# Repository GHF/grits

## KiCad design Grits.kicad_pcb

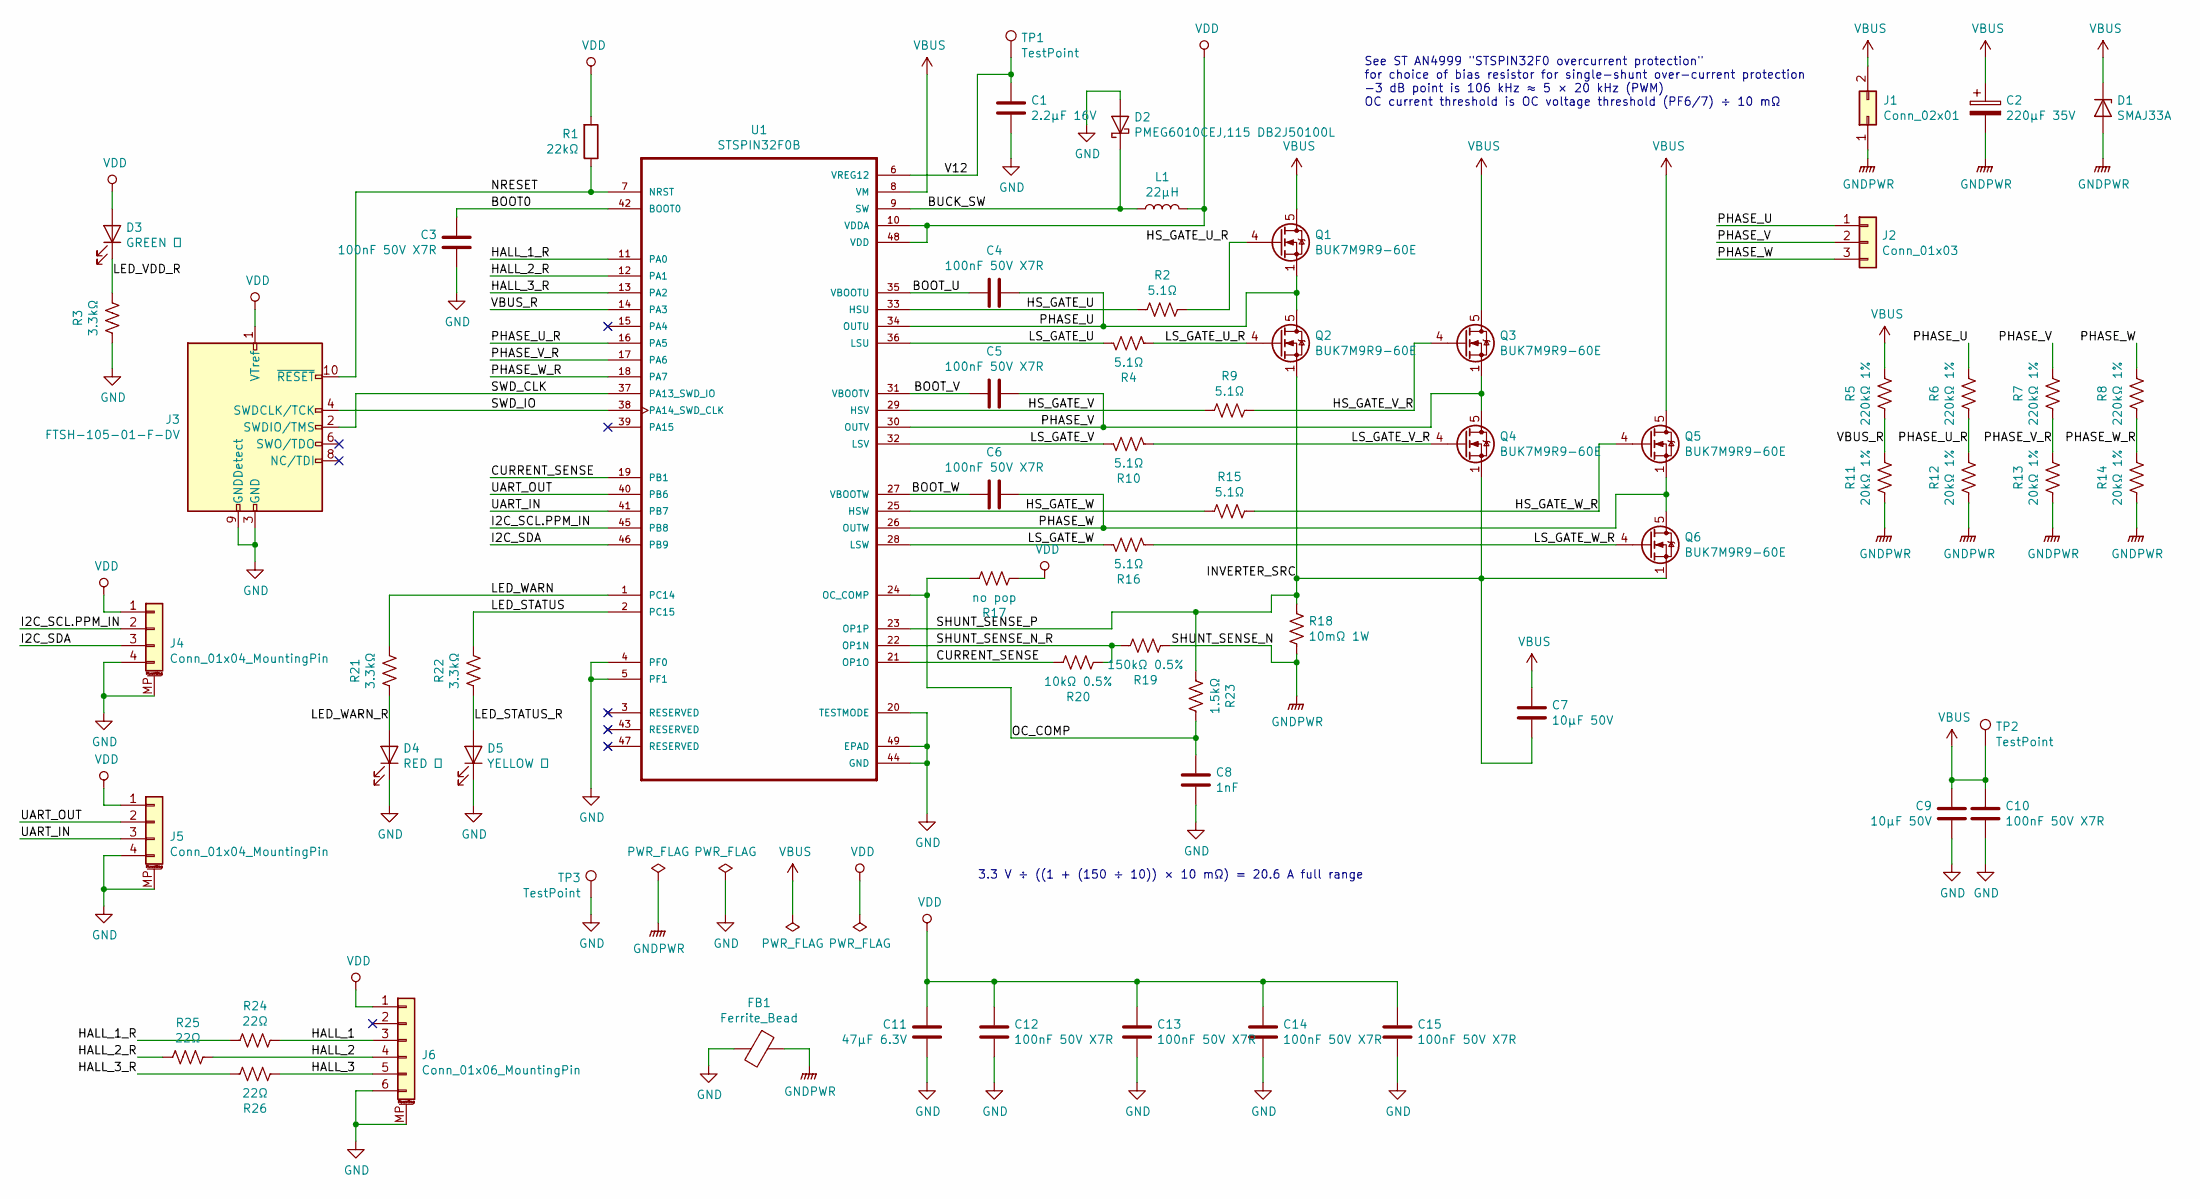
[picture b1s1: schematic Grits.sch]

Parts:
C1: 2.2µF 16V; C_0603_1608Metric
C2: 220µF 35V; CP_Elec_8x10.5
C3, C4, C5, C6, C10, C12, C13, C14, C15: 100nF 50V X7R; C_0603_1608Metric
C7, C9: 10µF 50V; C_1206_3216Metric
C8: 1nF; C_0603_1608Metric
C11: 47µF 6.3V; C_0805_2012Metric
D1: SMAJ33A; D_SMA
D2: PMEG6010CEJ,115 DB2J50100L; D_SOD-323F
D3: GREEN 绿; LED_0805_2012Metric
D4: RED 红; LED_0805_2012Metric
D5: YELLOW 黄; LED_0805_2012Metric
FB1: Ferrite_Bead; L_0603_1608Metric
J1: Conn_02x01; Molex_Micro-Fit_3.0_43045-0200_2x01_P3.00mm_Horizontal
J2: Conn_01x03; Molex_Micro-Fit_3.0_43650-0300_1x03_P3.00mm_Horizontal
J3: FTSH-105-01-F-DV; PinHeader_2x05_P1.27mm_Vertical_SMD
J4, J5: Conn_01x04_MountingPin; JST_GH_SM04B-GHS-TB_1x04-1MP_P1.25mm_Horizontal
J6: Conn_01x06_MountingPin; JST_GH_BM06B-GHS-TBT_1x06-1MP_P1.25mm_Vertical
L1: 22µH; L_1008_2520Metric
Q1, Q2, Q3, Q4, Q5, Q6: BUK7M9R9-60E; LFPAK33
R1: 22kΩ; R_0603_1608Metric
R2, R4, R9, R10, R15, R16: 5.1Ω; R_0603_1608Metric
R3, R21, R22: 3.3kΩ; R_0603_1608Metric
R5, R6, R7, R8: 220kΩ 1%; R_0603_1608Metric
R11, R12, R13, R14: 20kΩ 1%; R_0603_1608Metric
R17: no pop; R_0603_1608Metric
R18: 10mΩ 1W; R_1206_3216Metric
R19: 150kΩ 0.5%; R_0603_1608Metric
R20: 10kΩ 0.5%; R_0603_1608Metric
R23: 1.5kΩ; R_0603_1608Metric
R24, R25, R26: 22Ω; R_0603_1608Metric
TP1, TP2, TP3: TestPoint; TestPoint_Pad_D1.0mm
U1: STSPIN32F0B; VQFN-48-1EP_7x7mm_P0.5mm_EP2.8x2.8mm

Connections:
/BOOT0: C3.2, U1.42 (BOOT0)
/BOOT_U: C4.2, U1.35 (VBOOTU)
/BOOT_V: C5.2, U1.31 (VBOOTV)
/BOOT_W: C6.2, U1.27 (VBOOTW)
/BUCK_SW: D2.1 (K), L1.1, U1.9 (SW)
/CURRENT_SENSE: R20.1, U1.19 (PB1), U1.21 (OP1O)
/HALL_1: J6.3, R24.1
/HALL_1_R: R24.2, U1.11 (PA0)
/HALL_2: J6.4, R25.1
/HALL_2_R: R25.2, U1.12 (PA1)
/HALL_3: J6.5, R26.2
/HALL_3_R: R26.1, U1.13 (PA2)
/HS_GATE_U: R2.2, U1.33 (HSU)
/HS_GATE_U_R: Q1.4 (G), R2.1
/HS_GATE_V: R9.2, U1.29 (HSV)
/HS_GATE_V_R: Q3.4 (G), R9.1
/HS_GATE_W: R15.2, U1.25 (HSW)
/HS_GATE_W_R: Q5.4 (G), R15.1
/I2C_SCL.PPM_IN: J4.2, U1.45 (PB8)
/I2C_SDA: J4.3, U1.46 (PB9)
/INVERTER_SRC: C7.2, Q2.1 (S), Q2.2 (S), Q2.3 (S), Q4.1 (S), Q4.2 (S), Q4.3 (S), Q6.1 (S), Q6.2 (S), Q6.3 (S), R18.1, R23.2, U1.23 (OP1P)
/LED_STATUS: R22.1, U1.2 (PC15)
/LED_STATUS_R: D5.2 (A), R22.2
/LED_VDD_R: D3.1 (K), R3.1
/LED_WARN: R21.1, U1.1 (PC14)
/LED_WARN_R: D4.2 (A), R21.2
/LS_GATE_U: R4.2, U1.36 (LSU)
/LS_GATE_U_R: Q2.4 (G), R4.1
/LS_GATE_V: R10.2, U1.32 (LSV)
/LS_GATE_V_R: Q4.4 (G), R10.1
/LS_GATE_W: R16.2, U1.28 (LSW)
/LS_GATE_W_R: Q6.4 (G), R16.1
/NRESET: J3.10 (~RESET~), R1.1, U1.7 (NRST)
/OC_COMP: C8.1, R17.1, R23.1, U1.24 (OC_COMP)
/PHASE_U: C4.1, J2.1, Q1.1 (S), Q1.2 (S), Q1.3 (S), Q2.5 (D), R6.1, U1.34 (OUTU)
/PHASE_U_R: R6.2, R12.1, U1.16 (PA5)
/PHASE_V: C5.1, J2.2, Q3.1 (S), Q3.2 (S), Q3.3 (S), Q4.5 (D), R7.1, U1.30 (OUTV)
/PHASE_V_R: R7.2, R13.1, U1.17 (PA6)
/PHASE_W: C6.1, J2.3, Q5.1 (S), Q5.2 (S), Q5.3 (S), Q6.5 (D), R8.1, U1.26 (OUTW)
/PHASE_W_R: R8.2, R14.1, U1.18 (PA7)
/SHUNT_SENSE_N_R: R19.1, R20.2, U1.22 (OP1N)
/SWD_CLK: J3.2 (SWDIO/TMS), U1.37 (PA13_SWD_IO)
/SWD_IO: J3.4 (SWDCLK/TCK), U1.38 (PA14_SWD_CLK)
/UART_IN: J5.3, U1.41 (PB7)
/UART_OUT: J5.2, U1.40 (PB6)
/V12: C1.1, TP1.1, U1.6 (VREG12)
/VBUS_R: R5.2, R11.1, U1.14 (PA3)
GND: C1.2, C3.1, C8.2, C9.2, C10.2, C11.2, C12.2, C13.2, C14.2, C15.2, D2.2 (A), D4.1 (K), D5.1 (K), FB1.2, J3.3 (GND), J3.5 (GND), J3.9 (GNDDetect), J4.4, J4.MP (MountPin), J5.4, J5.MP (MountPin), J6.6, J6.MP (MountPin), R3.2, TP3.1, U1.4 (PF0), U1.5 (PF1), U1.20 (TESTMODE), U1.44 (GND), U1.49 (EPAD)
GNDPWR: C2.2, D1.2 (A), FB1.1, J1.1, R11.2, R12.2, R13.2, R14.2, R18.2, R19.2
VBUS: C2.1, C7.1, C9.1, C10.1, D1.1 (K), J1.2, Q1.5 (D), Q3.5 (D), Q5.5 (D), R5.1, TP2.1, U1.8 (VM)
VDD: C11.1, C12.1, C13.1, C14.1, C15.1, D3.2 (A), J3.1 (VTref), J4.1, J5.1, J6.1, L1.2, R1.2, R17.2, U1.10 (VDDA), U1.48 (VDD)

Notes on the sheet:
See ST AN4999 "STSPIN32F0 overcurrent protection" for choice of bias resistor for single-shunt over-current protection -3 dB point is 106 kHz ≈ 5 × 20 kHz (PWM) OC current threshold is OC voltage threshold (PF6/7) ÷ 10 mΩ
3.3 V ÷ ((1 + (150 ÷ 10)) × 10 mΩ) = 20.6 A full range

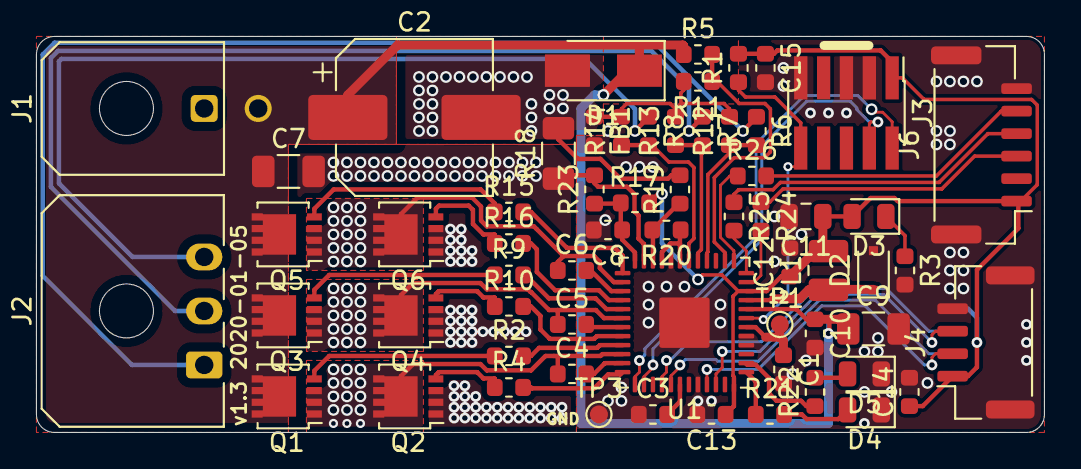
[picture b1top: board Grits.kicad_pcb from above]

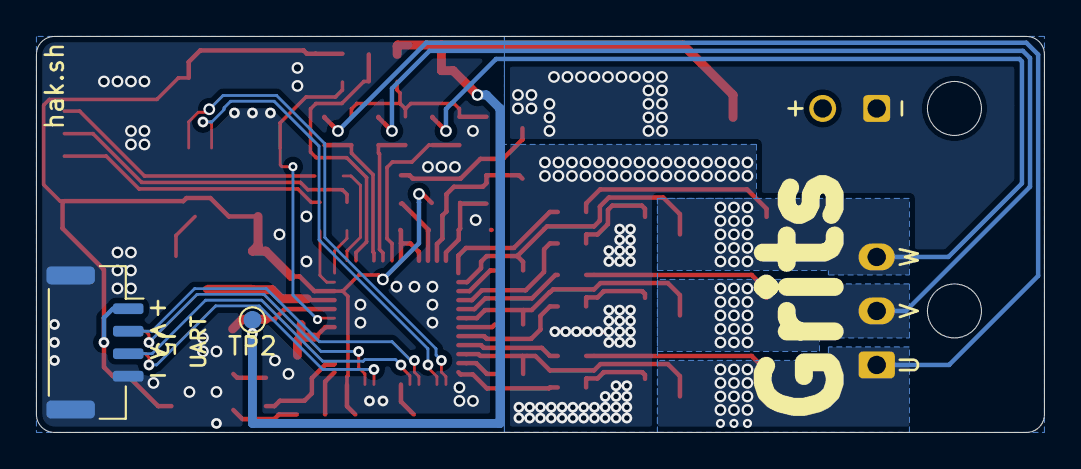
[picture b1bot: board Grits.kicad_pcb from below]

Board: 2 copper layers, 56.0 x 22.0 mm, 64 parts (2 on the bottom side), 51 nets.

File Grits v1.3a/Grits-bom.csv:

Comment,Designator,Footprint,LCSC Part #
"PMEG6010CEJ,115 DB2J50100L",D2,D_SOD-323F,C406049
TestPoint,"TP3,TP2,TP1",TestPoint_Pad_D1.0mm,
3.3kΩ,"R3,R22,R21",0603_R,C22978
GREEN 绿,D3,LED_0805_2012Metric,C2297
Conn_01x04_MountingPin,"J5,J4",JST_GH_SM04B-GHS-TB_1x04-1MP_P1.25mm_Horizontal,
STSPIN32F0B,U1,VQFN-48-1EP_7x7mm_P0.5mm_EP2.8x2.8mm,
FTSH-105-01-F-DV,J3,PinHeader_2x05_P1.27mm_Vertical_SMD,
BUK7M9R9-60E,"Q6,Q5,Q4,Q3,Q2,Q1",LFPAK33,
1.5kΩ,R23,0603_R,C22843
22kΩ,R1,0603_R,C31850
5.1Ω,"R16,R10,R4,R15,R9,R2",0603_R,C25197
22Ω,"R26,R25,R24",0603_R,C23345
10kΩ 0.5%,R20,0603_R,C25804
150kΩ 0.5%,R19,0603_R,C22807
10mΩ 1W,R18,R_1206_3216Metric,C76294
no pop,R17,0603_R,
20kΩ 1%,"R14,R13,R12,R11",0603_R,C4184
220kΩ 1%,"R8,R7,R6,R5",0603_R,C22961
22µH,L1,L_1008_2520Metric,
Conn_01x03,J2,Molex_Micro-Fit_3.0_43650-0300_1x03_P3.00mm_Horizontal,
Conn_02x01,J1,Molex_Micro-Fit_3.0_43045-0200_2x01_P3.00mm_Horizontal,
Conn_01x06_MountingPin,J6,JST_GH_BM06B-GHS-TBT_1x06-1MP_P1.25mm_Vertical,
Ferrite_Bead,FB1,L_0603_1608Metric,C85831
SMAJ33A,D1,D_SMA,C134981
YELLOW 黄,D5,LED_0805_2012Metric,C2296
RED 红,D4,LED_0805_2012Metric,C84256
100nF 50V X7R,"C10,C6,C5,C4,C15,C14,C13,C12,C3",0603_C,C14663
10µF 50V,C9,C_1206_3216Metric,C13585
220µF 35V,C2,CP_Elec_8x10.5,C134820
10uF 50V,C7,C_1206_3216Metric,C13585
1nF,C8,0603_C,C1588
2.2µF 16V,C1,0603_C,C23630
47µF 6.3V,C11,0805_C,C16780

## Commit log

2020-01-04 ✨ Add v1.0c
2020-01-04 ♻️ Clean up rev A and B
2020-01-04 ✨ Add v1.1
    Featuring rotated Hall connector going to different timer inputs
2020-01-05 ✨ Add v1.3a (DFM)
    v1.2: Retooled for DFM through JLCPCB
    v1.3: Fix bootstrap capacitor wiring error
